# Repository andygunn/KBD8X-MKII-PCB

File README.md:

# KBD8X-MKII-PCB
This is the source for the PCB used in the [KBD8X MKII by KBDfans](https://kbdfans.com/collections/kbd8x-mkii/products/coming-soon-kbd8x-mkii-custom-mechanical-keyboard-kit) by [ai03](https://kb.ai03.me). There have been a number of modifications to this PCB:
- Changed the MX-only footprints to MX/Alps-compatible footprints.
- Modified the routing of traces to accomodate the new footprints.
- Changed the ATmega32U4 from the -MU variety to the -AU variety so it could be hand-soldered (due to component shortages)

This PCB should work with the same firmware files as the original PCB, as the MCU and matrix are the same.

Note that this PCB is offered as-is with NO WARRANTY. If you produce it, you may encounter problems.

Please verify the conditions of the [license](https://github.com/ai03-2725/KBD8X-MKII-PCB/blob/master/LICENSE) before using.

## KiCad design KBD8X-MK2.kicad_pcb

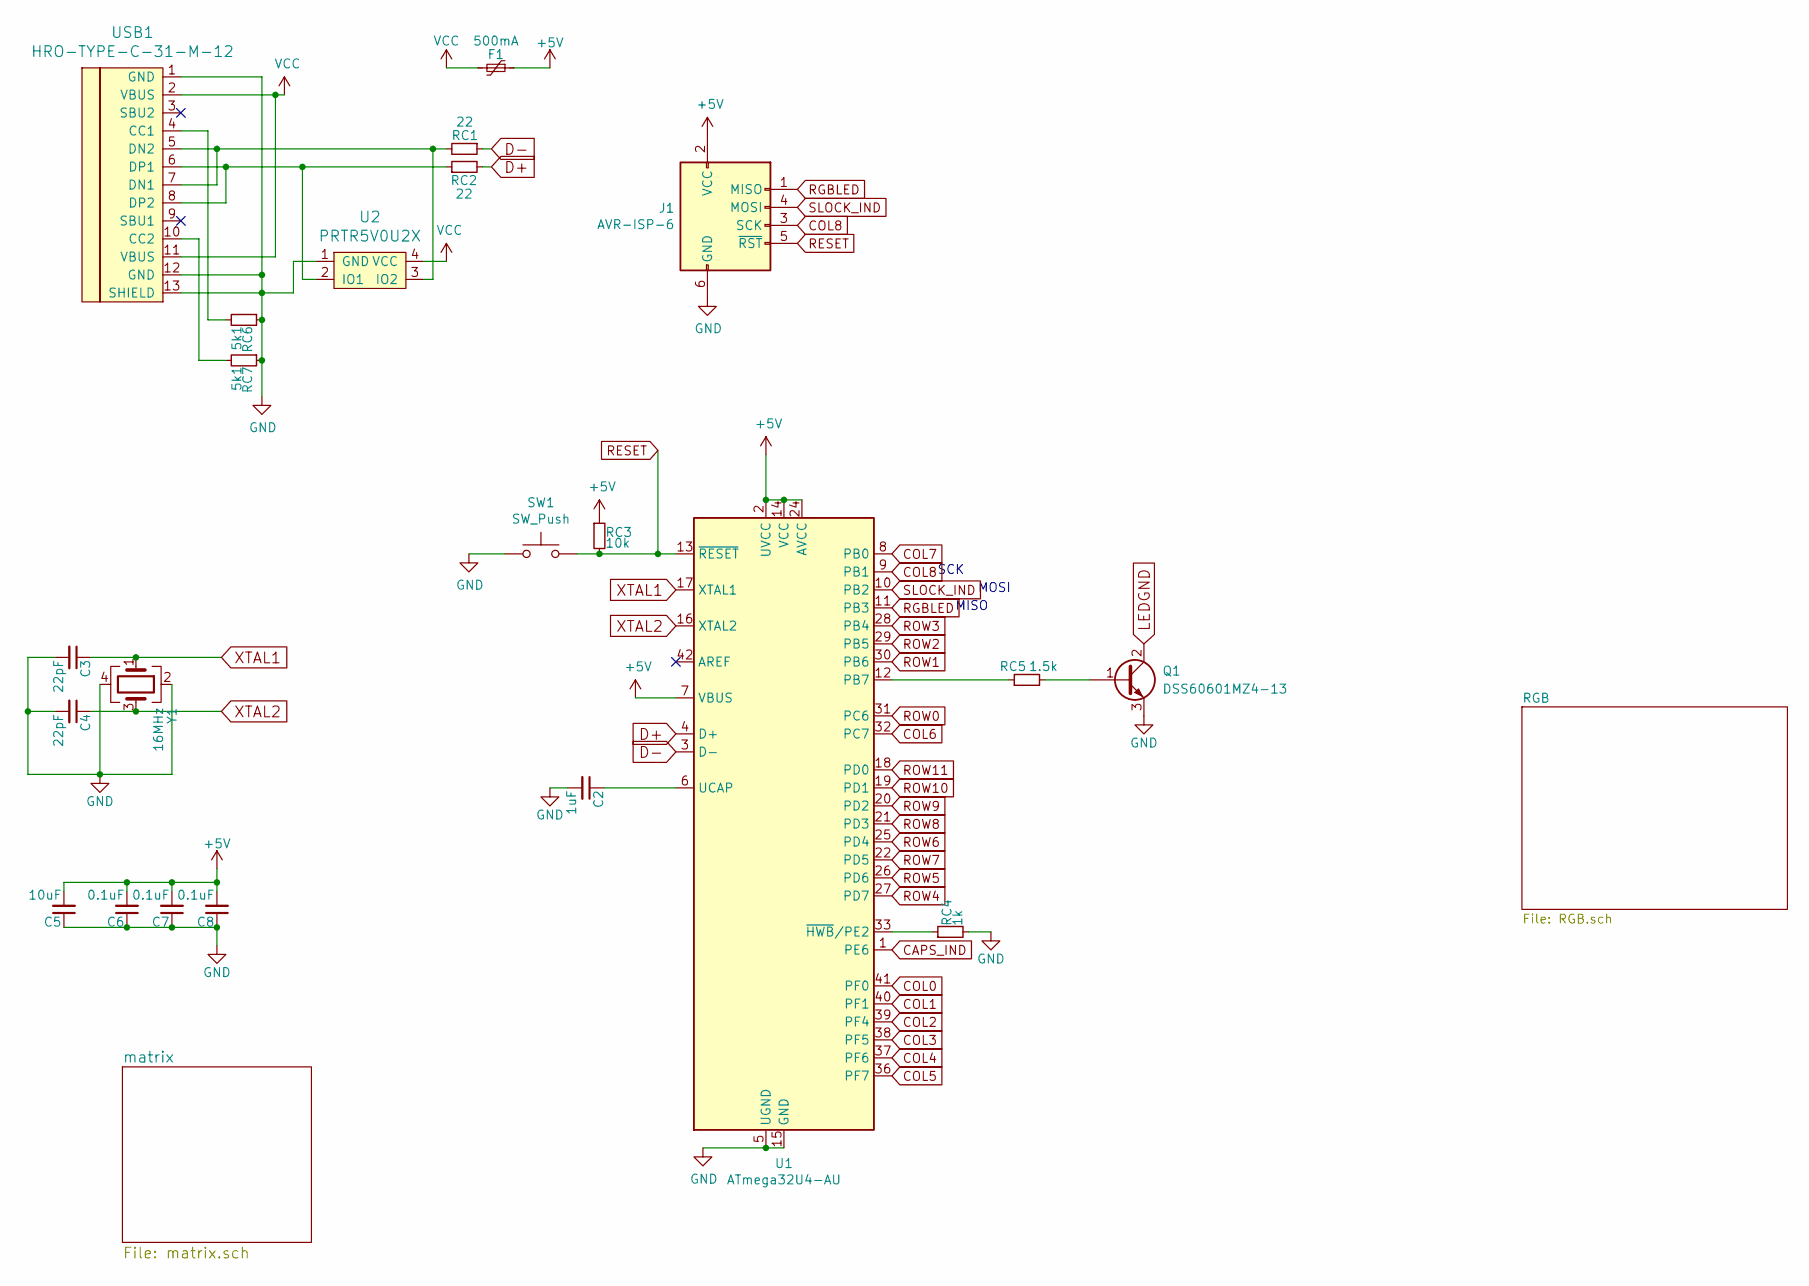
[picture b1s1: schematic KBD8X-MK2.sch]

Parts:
C2: 1uF; C_0603
C3, C4: 22pF; C_0603
C5: 10uF; C_0603
C6, C7, C8: 0.1uF; C_0603
F1: 500mA; Fuse_SMD1206_Wave
J1: AVR-ISP-6; Reset_Pretty-Mask
Q1: DSS60601MZ4-13; SOT-223-3_TabPin2
RC1, RC2: 22; R_0603
RC3: 10k; R_0603
RC4: 1k; R_0603
RC5: 1.5k; R_0603
RC6, RC7: 5k1; R_0603
SW1: SW_Push; SKQG-1155865
U1: ATmega32U4-AU; TQFP-44_10x10mm_P0.8mm
U2: PRTR5V0U2X; SOT143B
USB1: HRO-TYPE-C-31-M-12; HRO-TYPE-C-31-M-12-Assembly
Y1: 16MHz; Crystal_SMD_3225-4pin_3.2x2.5mm

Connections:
+5V: C5.2, C6.2, C7.2, C8.2, F1.1, J1.2 (VCC), RC3.1, U1.2 (UVCC), U1.7 (VBUS), U1.14 (VCC), U1.24 (AVCC), U1.34 (VCC), U1.44 (AVCC); also elsewhere on the board
CAPS_IND: U1.1 (PE6); also elsewhere on the board
COL0: U1.41 (PF0); also elsewhere on the board
COL1: U1.40 (PF1); also elsewhere on the board
COL2: U1.39 (PF4); also elsewhere on the board
COL3: U1.38 (PF5); also elsewhere on the board
COL4: U1.37 (PF6); also elsewhere on the board
COL5: U1.36 (PF7); also elsewhere on the board
COL6: U1.32 (PC7); also elsewhere on the board
COL7: U1.8 (PB0); also elsewhere on the board
COL8: J1.3 (SCK), U1.9 (PB1); also elsewhere on the board
D+: RC2.2, U1.4 (D+)
D-: RC1.1, U1.3 (D-)
GND: C2.2, C3.2, C4.2, C5.1, C6.1, C7.1, C8.1, J1.6 (GND), Q1.3 (E), RC4.2, RC6.1, RC7.1, SW1.1, U1.5 (UGND), U1.15 (GND), U1.23 (GND), U1.35 (GND), U1.43 (GND), U1.45 (GND), U2.1 (GND), USB1.1 (GND), USB1.12 (GND), USB1.13 (SHIELD), Y1.2, Y1.4; also elsewhere on the board
LEDGND: Q1.2 (C); also elsewhere on the board
unnamed: C2.1, U1.6 (UCAP)
unnamed: Q1.1 (B), RC5.2
unnamed: RC1.2, U2.3 (IO2), USB1.5 (DN2), USB1.7 (DN1)
unnamed: RC2.1, U2.2 (IO1), USB1.6 (DP1), USB1.8 (DP2)
unnamed: RC4.1, U1.33 (~HWB~/PE2)
unnamed: RC5.1, U1.12 (PB7)
unnamed: RC6.2, USB1.4 (CC1)
unnamed: RC7.2, USB1.10 (CC2)
RESET: J1.5 (~RST), RC3.2, SW1.2, U1.13 (~RESET)
RGBLED: J1.1 (MISO), U1.11 (PB3); also elsewhere on the board
ROW0: U1.31 (PC6); also elsewhere on the board
ROW1: U1.30 (PB6); also elsewhere on the board
ROW2: U1.29 (PB5); also elsewhere on the board
ROW3: U1.28 (PB4); also elsewhere on the board
ROW4: U1.27 (PD7); also elsewhere on the board
ROW5: U1.26 (PD6); also elsewhere on the board
ROW6: U1.25 (PD4); also elsewhere on the board
ROW7: U1.22 (PD5); also elsewhere on the board
ROW8: U1.21 (PD3); also elsewhere on the board
ROW9: U1.20 (PD2); also elsewhere on the board
ROW10: U1.19 (PD1); also elsewhere on the board
ROW11: U1.18 (PD0); also elsewhere on the board
SLOCK_IND: J1.4 (MOSI), U1.10 (PB2); also elsewhere on the board
VCC: F1.2, U2.4 (VCC), USB1.2 (VBUS), USB1.11 (VBUS)
XTAL1: C3.1, U1.17 (XTAL1), Y1.1
XTAL2: C4.1, U1.16 (XTAL2), Y1.3

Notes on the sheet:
MOSI
MISO
SCK

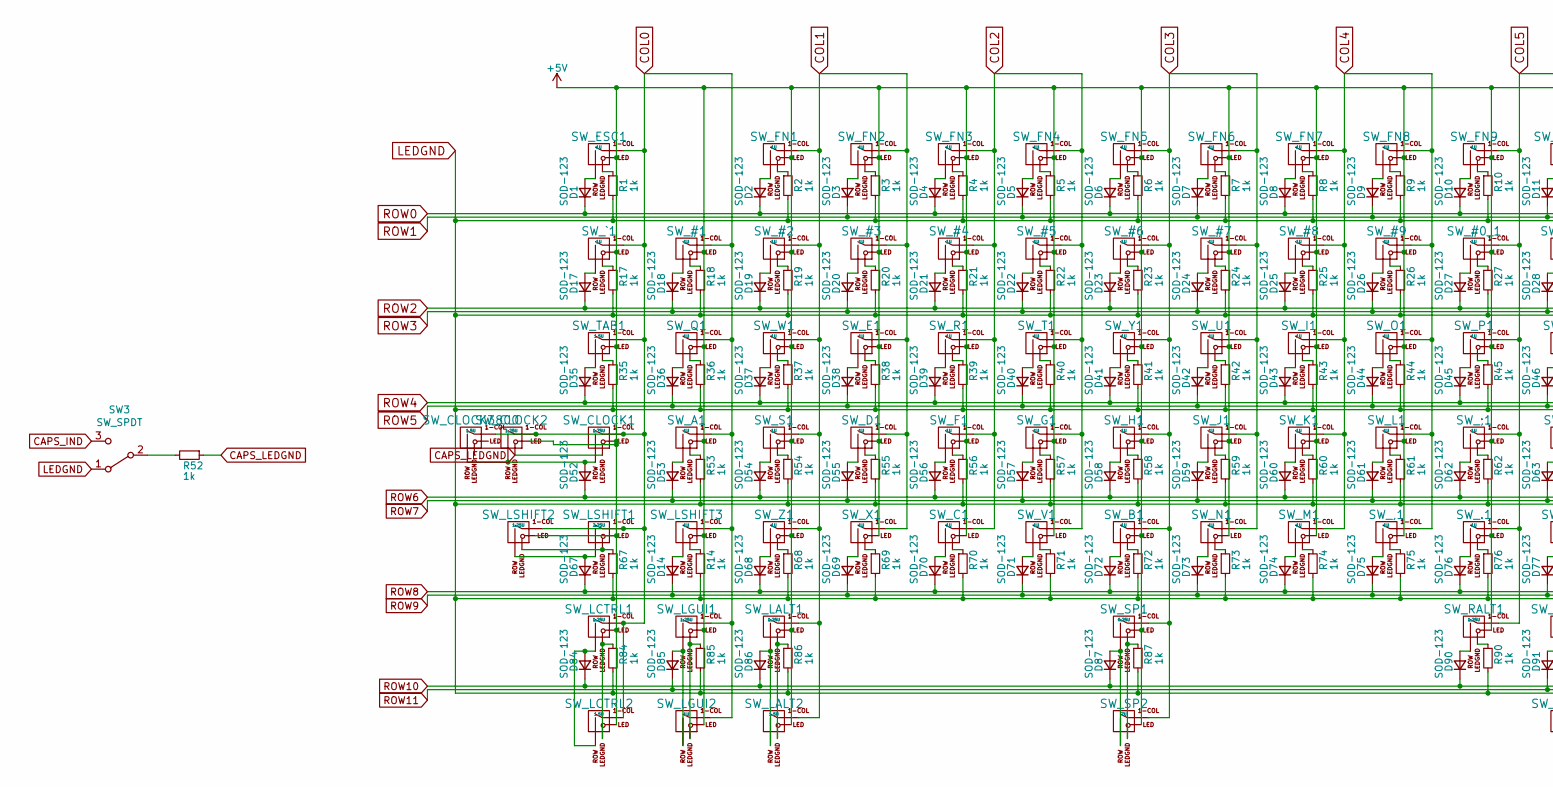
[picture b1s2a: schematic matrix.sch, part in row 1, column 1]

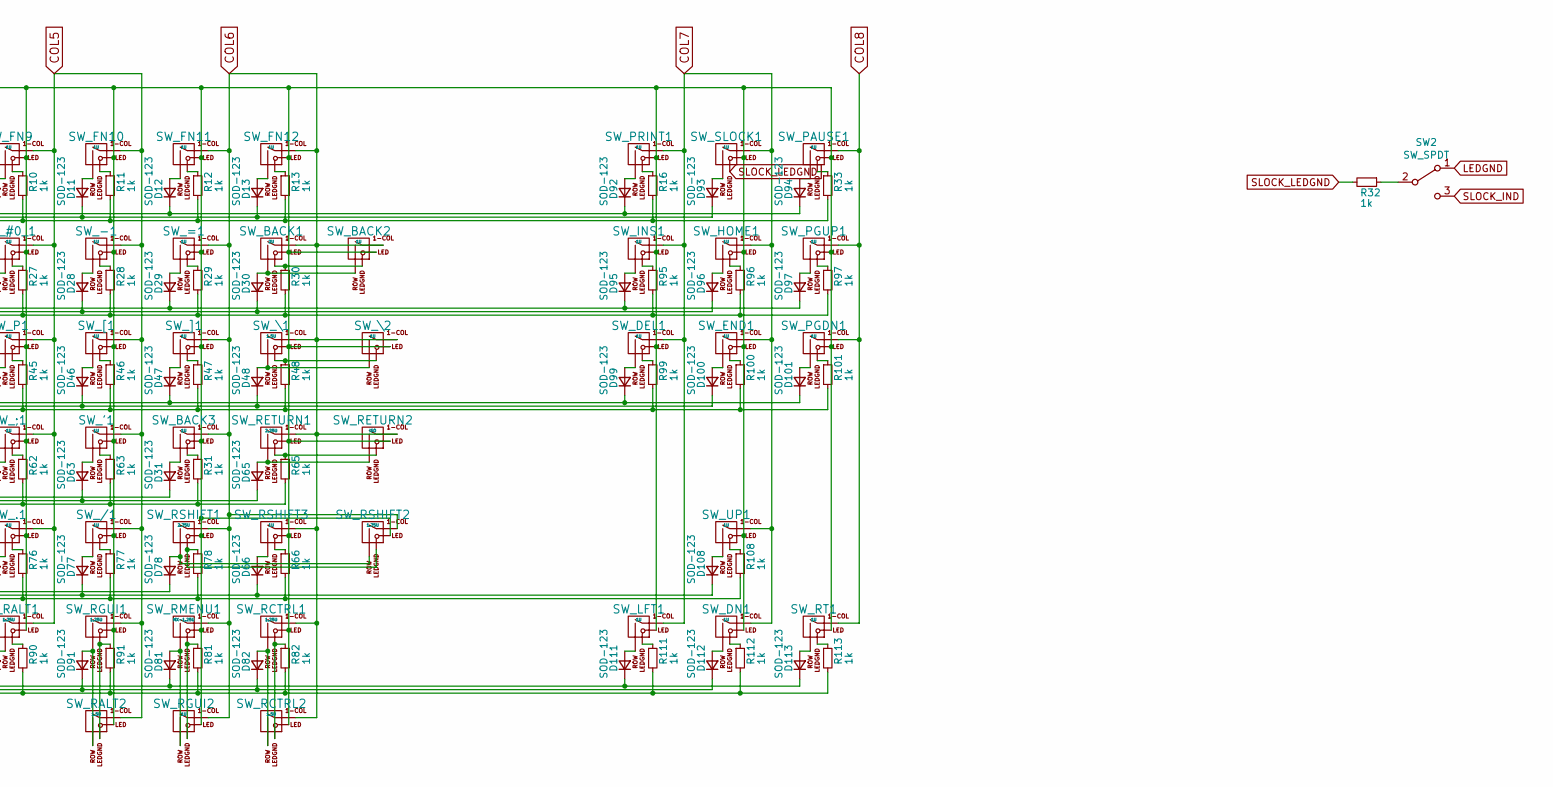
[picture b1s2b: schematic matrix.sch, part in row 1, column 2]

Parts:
D1, D2, D3, D4, D5, D6, D7, D8, D9, D10, D11, D12, D13, D14, D17, D18, D19, D20, D21, D22, D23, D24, D25, D26, D27, D28, D29, D30, D31, D35, D36, D37, D38, D39, D40, D41, D42, D43, D44, D45, D46, D47, D48, D52, D53, D54, D55, D56, D57, D58, D59, D60, D61, D62, D63, D65, D66, D67, D68, D69, D70, D71, D72, D73, D74, D75, D76, D77, D78, D81, D82, D84, D85, D86, D87, D90, D91, D92, D93, D94, D95, D96, D97, D99, D100, D101, D108, D111, D112, D113: SOD-123; D_SOD-123
R1, R2, R3, R4, R5, R6, R7, R8, R9, R10, R11, R12, R13, R14, R16, R17, R18, R19, R20, R21, R22, R23, R24, R25, R26, R27, R28, R29, R30, R31, R32, R33, R35, R36, R37, R38, R39, R40, R41, R42, R43, R44, R45, R46, R47, R48, R52, R53, R54, R55, R56, R57, R58, R59, R60, R61, R62, R63, R65, R66, R67, R68, R69, R70, R71, R72, R73, R74, R75, R76, R77, R78, R81, R82, R84, R85, R86, R87, R90, R91, R95, R96, R97, R99, R100, R101, R108, R111, R112, R113: 1k; R_0603
SW2, SW3: SW_SPDT; SW_SPDT_PCM12
SW_#0_1, SW_#1, SW_#2, SW_#3, SW_#4, SW_#5, SW_#6, SW_#7, SW_#8, SW_#9: 1U; MX-1U
SW_'1: 1U; MX-1U
SW_,1: 1U; MX-1U
SW_-1: 1U; MX-1U
SW_.1: 1U; MX-1U
SW_/1: 1U; MX-1U
SW_;1: 1U; MX-1U
SW_=1: 1U; MX-1U
SW_A1: 1U; MX-1U
SW_B1: 1U; MX-1U
SW_BACK1: 2U; MX-2U
SW_BACK2, SW_BACK3: 1U; MX-1U
SW_C1: 1U; MX-1U
SW_CLOCK1: 1.75U; MX-1.75U
SW_CLOCK2: 1.25U; MX-1.25U-FLIPPED
SW_CLOCK3800: 1.5U; ALPS-1.5U
SW_D1: 1U; MX-1U
SW_DEL1: 1U; MX-1U
SW_DN1: 1U; MX-1U
SW_E1: 1U; MX-1U
SW_END1: 1U; MX-1U
SW_ESC1: 1U; MX-1U
SW_F1: 1U; MX-1U
SW_FN1, SW_FN2, SW_FN3, SW_FN4, SW_FN5, SW_FN6, SW_FN7, SW_FN8, SW_FN9, SW_FN10, SW_FN11, SW_FN12: 1U; MX-1U
SW_G1: 1U; MX-1U
SW_H1: 1U; MX-1U
SW_HOME1: 1U; MX-1U
SW_I1: 1U; MX-1U
SW_INS1: 1U; MX-1U
SW_J1: 1U; MX-1U
SW_K1: 1U; MX-1U
SW_L1: 1U; MX-1U
SW_LALT1: 1.25U; MX-1.25U
SW_LALT2: 1.5U; MX-1.5U-FLIPPED
SW_LCTRL1: 1.25U; MX-1.25U
SW_LCTRL2: 1.5U; MX-1.5U-FLIPPED
SW_LFT1: 1U; MX-1U
SW_LGUI1: 1.25U; MX-1.25U
SW_LGUI2: 1U; MX-1U-FLIPPED
SW_LSHIFT1: 2.25U; MX-2.25U
SW_LSHIFT2: 1.25U; MX-1.25U
SW_LSHIFT3: 1U; MX-1U
SW_M1: 1U; MX-1U
SW_N1: 1U; MX-1U
SW_O1: 1U; MX-1U
SW_P1: 1U; MX-1U
SW_PAUSE1: 1U; MX-1U
SW_PGDN1: 1U; MX-1U
SW_PGUP1: 1U; MX-1U
SW_PRINT1: 1U; MX-1U
SW_Q1: 1U; MX-1U
SW_R1: 1U; MX-1U
SW_RALT1: 1.25U; MX-1.25U
SW_RALT2: 1.5U; MX-1.5U
SW_RCTRL1: 1.25U; MX-1.25U-FLIPPED
SW_RCTRL2: 1.5U; MX-1.5U
SW_RETURN1: 2.25U; MX-2.25U
SW_RETURN2: ISO; MX-ISO-ReversedStabilizers
SW_RGUI1: 1.25U; MX-1.25U-FLIPPED
SW_RGUI2: 1U; MX-1U
SW_RMENU1: MX-1.25U; MX-1.25U-FLIPPED
SW_RSHIFT1: 2.75U; MX-2.75U
SW_RSHIFT2: 1.75U; MX-1.75U
SW_RSHIFT3: 1U; MX-1U
SW_RT1: 1U; MX-1U
SW_S1: 1U; MX-1U
SW_SLOCK1: 1U; MX-1U
SW_SP1: 6.25U; MX-6.25U-ReversedStabilizers
SW_SP2: 7U; MX-7U-ReversedStabilizers
SW_T1: 1U; MX-1U
SW_TAB1: 1.5U; MX-1.5U
SW_U1: 1U; MX-1U
SW_UP1: 1U; MX-1U
SW_V1: 1U; MX-1U
SW_W1: 1U; MX-1U
SW_X1: 1U; MX-1U
SW_Y1: 1U; MX-1U
SW_Z1: 1U; MX-1U
SW_[1: 1U; MX-1U
SW_\1: 1.5U; MX-1.5U
SW_\2: 1U; MX-1U
SW_]1: 1U; MX-1U
SW_`1: 1U; MX-1U

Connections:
+5V: SW_#0_1.3 (LED), SW_#1.3 (LED), SW_#2.3 (LED), SW_#3.3 (LED), SW_#4.3 (LED), SW_#5.3 (LED), SW_#6.3 (LED), SW_#7.3 (LED), SW_#8.3 (LED), SW_#9.3 (LED), SW_'1.3 (LED), SW_,1.3 (LED), SW_-1.3 (LED), SW_.1.3 (LED), SW_/1.3 (LED), SW_;1.3 (LED), SW_=1.3 (LED), SW_A1.3 (LED), SW_B1.3 (LED), SW_BACK1.3 (LED), SW_BACK2.3 (LED), SW_BACK3.3 (LED), SW_C1.3 (LED), SW_CLOCK1.3 (LED), SW_CLOCK2.3 (LED), SW_D1.3 (LED), SW_DEL1.3 (LED), SW_DN1.3 (LED), SW_E1.3 (LED), SW_END1.3 (LED), SW_ESC1.3 (LED), SW_F1.3 (LED), SW_FN1.3 (LED), SW_FN2.3 (LED), SW_FN3.3 (LED), SW_FN4.3 (LED), SW_FN5.3 (LED), SW_FN6.3 (LED), SW_FN7.3 (LED), SW_FN8.3 (LED), SW_FN9.3 (LED), SW_FN10.3 (LED), SW_FN11.3 (LED), SW_FN12.3 (LED), SW_G1.3 (LED), SW_H1.3 (LED), SW_HOME1.3 (LED), SW_I1.3 (LED), SW_INS1.3 (LED), SW_J1.3 (LED), SW_K1.3 (LED), SW_L1.3 (LED), SW_LALT1.3 (LED), SW_LALT2.3 (LED), SW_LCTRL1.3 (LED), SW_LCTRL2.3 (LED), SW_LFT1.3 (LED), SW_LGUI1.3 (LED), SW_LGUI2.3 (LED), SW_LSHIFT1.3 (LED), SW_LSHIFT2.3 (LED), SW_LSHIFT3.3 (LED), SW_M1.3 (LED), SW_N1.3 (LED), SW_O1.3 (LED), SW_P1.3 (LED), SW_PAUSE1.3 (LED), SW_PGDN1.3 (LED), SW_PGUP1.3 (LED), SW_PRINT1.3 (LED), SW_Q1.3 (LED), SW_R1.3 (LED), SW_RALT1.3 (LED), SW_RALT2.3 (LED), SW_RCTRL1.3 (LED), SW_RCTRL2.3 (LED), SW_RETURN1.3 (LED), SW_RETURN2.3 (LED), SW_RGUI1.3 (LED), SW_RGUI2.3 (LED), SW_RMENU1.3 (LED), SW_RSHIFT1.3 (LED), SW_RSHIFT2.3 (LED), SW_RSHIFT3.3 (LED), SW_RT1.3 (LED), SW_S1.3 (LED), SW_SLOCK1.3 (LED), SW_SP1.3 (LED), SW_SP2.3 (LED), SW_T1.3 (LED), SW_TAB1.3 (LED), SW_U1.3 (LED), SW_UP1.3 (LED), SW_V1.3 (LED), SW_W1.3 (LED), SW_X1.3 (LED), SW_Y1.3 (LED), SW_Z1.3 (LED), SW_[1.3 (LED), SW_\1.3 (LED), SW_\2.3 (LED), SW_]1.3 (LED), SW_`1.3 (LED); also elsewhere on the board
CAPS_IND: SW3.3 (C); also elsewhere on the board
CAPS_LEDGND: R52.1, SW_CLOCK1.4 (LEDGND), SW_CLOCK2.4 (LEDGND)
COL0: SW_#1.1 (COL), SW_A1.1 (COL), SW_CLOCK1.1 (COL), SW_CLOCK2.1 (COL), SW_CLOCK3800.1 (COL), SW_ESC1.1 (COL), SW_LCTRL1.1 (COL), SW_LCTRL2.1 (COL), SW_LGUI1.1 (COL), SW_LGUI2.1 (COL), SW_LSHIFT1.1 (COL), SW_LSHIFT2.1 (COL), SW_LSHIFT3.1 (COL), SW_Q1.1 (COL), SW_TAB1.1 (COL), SW_`1.1 (COL); also elsewhere on the board
COL1: SW_#2.1 (COL), SW_#3.1 (COL), SW_D1.1 (COL), SW_E1.1 (COL), SW_FN1.1 (COL), SW_FN2.1 (COL), SW_LALT1.1 (COL), SW_LALT2.1 (COL), SW_S1.1 (COL), SW_W1.1 (COL), SW_X1.1 (COL), SW_Z1.1 (COL); also elsewhere on the board
COL2: SW_#4.1 (COL), SW_#5.1 (COL), SW_C1.1 (COL), SW_F1.1 (COL), SW_FN3.1 (COL), SW_FN4.1 (COL), SW_G1.1 (COL), SW_R1.1 (COL), SW_T1.1 (COL), SW_V1.1 (COL); also elsewhere on the board
COL3: SW_#6.1 (COL), SW_#7.1 (COL), SW_B1.1 (COL), SW_FN5.1 (COL), SW_FN6.1 (COL), SW_H1.1 (COL), SW_J1.1 (COL), SW_N1.1 (COL), SW_SP1.1 (COL), SW_SP2.1 (COL), SW_U1.1 (COL), SW_Y1.1 (COL); also elsewhere on the board
COL4: SW_#8.1 (COL), SW_#9.1 (COL), SW_,1.1 (COL), SW_FN7.1 (COL), SW_FN8.1 (COL), SW_I1.1 (COL), SW_K1.1 (COL), SW_L1.1 (COL), SW_M1.1 (COL), SW_O1.1 (COL); also elsewhere on the board
COL5: SW_#0_1.1 (COL), SW_'1.1 (COL), SW_-1.1 (COL), SW_.1.1 (COL), SW_/1.1 (COL), SW_;1.1 (COL), SW_FN9.1 (COL), SW_FN10.1 (COL), SW_P1.1 (COL), SW_RALT1.1 (COL), SW_RALT2.1 (COL), SW_RGUI1.1 (COL), SW_[1.1 (COL); also elsewhere on the board
COL6: SW_=1.1 (COL), SW_BACK1.1 (COL), SW_BACK2.1 (COL), SW_BACK3.1 (COL), SW_FN11.1 (COL), SW_FN12.1 (COL), SW_RCTRL1.1 (COL), SW_RCTRL2.1 (COL), SW_RETURN1.1 (COL), SW_RETURN2.1 (COL), SW_RGUI2.1 (COL), SW_RMENU1.1 (COL), SW_RSHIFT1.1 (COL), SW_RSHIFT2.1 (COL), SW_RSHIFT3.1 (COL), SW_\1.1 (COL), SW_\2.1 (COL), SW_]1.1 (COL); also elsewhere on the board
COL7: SW_DEL1.1 (COL), SW_DN1.1 (COL), SW_END1.1 (COL), SW_HOME1.1 (COL), SW_INS1.1 (COL), SW_LFT1.1 (COL), SW_PRINT1.1 (COL), SW_SLOCK1.1 (COL), SW_UP1.1 (COL); also elsewhere on the board
COL8: SW_PAUSE1.1 (COL), SW_PGDN1.1 (COL), SW_PGUP1.1 (COL), SW_RT1.1 (COL); also elsewhere on the board
LEDGND: R1.2, R2.2, R3.2, R4.2, R5.2, R6.2, R7.2, R8.2, R9.2, R10.2, R11.2, R12.2, R13.2, R14.2, R16.2, R17.2, R18.2, R19.2, R20.2, R21.2, R22.2, R23.2, R24.2, R25.2, R26.2, R27.2, R28.2, R29.2, R30.2, R31.2, R33.2, R35.2, R36.2, R37.2, R38.2, R39.2, R40.2, R41.2, R42.2, R43.2, R44.2, R45.2, R46.2, R47.2, R48.2, R53.2, R54.2, R55.2, R56.2, R57.2, R58.2, R59.2, R60.2, R61.2, R62.2, R63.2, R65.2, R66.2, R67.2, R68.2, R69.2, R70.2, R71.2, R72.2, R73.2, R74.2, R75.2, R76.2, R77.2, R78.2, R81.2, R82.2, R84.2, R85.2, R86.2, R87.2, R90.2, R91.2, R95.2, R96.2, R97.2, R99.2, R100.2, R101.2, R108.2, R111.2, R112.2, R113.2, SW2.1 (A), SW3.1 (A); also elsewhere on the board
unnamed: D1.2 (A), SW_ESC1.2 (ROW)
unnamed: D2.2 (A), SW_FN1.2 (ROW)
unnamed: D3.2 (A), SW_FN2.2 (ROW)
unnamed: D4.2 (A), SW_FN3.2 (ROW)
unnamed: D5.2 (A), SW_FN4.2 (ROW)
unnamed: D6.2 (A), SW_FN5.2 (ROW)
unnamed: D7.2 (A), SW_FN6.2 (ROW)
unnamed: D8.2 (A), SW_FN7.2 (ROW)
unnamed: D9.2 (A), SW_FN8.2 (ROW)
unnamed: D10.2 (A), SW_FN9.2 (ROW)
unnamed: D11.2 (A), SW_FN10.2 (ROW)
unnamed: D12.2 (A), SW_FN11.2 (ROW)
unnamed: D13.2 (A), SW_FN12.2 (ROW)
unnamed: D14.2 (A), SW_LSHIFT3.2 (ROW)
unnamed: D17.2 (A), SW_`1.2 (ROW)
unnamed: D18.2 (A), SW_#1.2 (ROW)
unnamed: D19.2 (A), SW_#2.2 (ROW)
unnamed: D20.2 (A), SW_#3.2 (ROW)
unnamed: D21.2 (A), SW_#4.2 (ROW)
unnamed: D22.2 (A), SW_#5.2 (ROW)
unnamed: D23.2 (A), SW_#6.2 (ROW)
unnamed: D24.2 (A), SW_#7.2 (ROW)
unnamed: D25.2 (A), SW_#8.2 (ROW)
unnamed: D26.2 (A), SW_#9.2 (ROW)
unnamed: D27.2 (A), SW_#0_1.2 (ROW)
unnamed: D28.2 (A), SW_-1.2 (ROW)
unnamed: D29.2 (A), SW_=1.2 (ROW)
unnamed: D30.2 (A), SW_BACK1.2 (ROW), SW_BACK2.2 (ROW)
unnamed: D31.2 (A), SW_BACK3.2 (ROW)
unnamed: D35.2 (A), SW_TAB1.2 (ROW)
unnamed: D36.2 (A), SW_Q1.2 (ROW)
unnamed: D37.2 (A), SW_W1.2 (ROW)
unnamed: D38.2 (A), SW_E1.2 (ROW)
unnamed: D39.2 (A), SW_R1.2 (ROW)
unnamed: D40.2 (A), SW_T1.2 (ROW)
unnamed: D41.2 (A), SW_Y1.2 (ROW)
unnamed: D42.2 (A), SW_U1.2 (ROW)
unnamed: D43.2 (A), SW_I1.2 (ROW)
unnamed: D44.2 (A), SW_O1.2 (ROW)
unnamed: D45.2 (A), SW_P1.2 (ROW)
unnamed: D46.2 (A), SW_[1.2 (ROW)
unnamed: D47.2 (A), SW_]1.2 (ROW)
unnamed: D48.2 (A), SW_\1.2 (ROW), SW_\2.2 (ROW)
unnamed: D52.2 (A), SW_CLOCK1.2 (ROW), SW_CLOCK2.2 (ROW), SW_CLOCK3800.2 (ROW)
unnamed: D53.2 (A), SW_A1.2 (ROW)
unnamed: D54.2 (A), SW_S1.2 (ROW)
unnamed: D55.2 (A), SW_D1.2 (ROW)
unnamed: D56.2 (A), SW_F1.2 (ROW)
unnamed: D57.2 (A), SW_G1.2 (ROW)
unnamed: D58.2 (A), SW_H1.2 (ROW)
unnamed: D59.2 (A), SW_J1.2 (ROW)
unnamed: D60.2 (A), SW_K1.2 (ROW)
unnamed: D61.2 (A), SW_L1.2 (ROW)
unnamed: D62.2 (A), SW_;1.2 (ROW)
unnamed: D63.2 (A), SW_'1.2 (ROW)
unnamed: D65.2 (A), SW_RETURN1.2 (ROW), SW_RETURN2.2 (ROW)
unnamed: D66.2 (A), SW_RSHIFT3.2 (ROW)
unnamed: D67.2 (A), SW_LSHIFT1.2 (ROW), SW_LSHIFT2.2 (ROW)
unnamed: D68.2 (A), SW_Z1.2 (ROW)
unnamed: D69.2 (A), SW_X1.2 (ROW)
unnamed: D70.2 (A), SW_C1.2 (ROW)
unnamed: D71.2 (A), SW_V1.2 (ROW)
unnamed: D72.2 (A), SW_B1.2 (ROW)
unnamed: D73.2 (A), SW_N1.2 (ROW)
unnamed: D74.2 (A), SW_M1.2 (ROW)
unnamed: D75.2 (A), SW_,1.2 (ROW)
unnamed: D76.2 (A), SW_.1.2 (ROW)
unnamed: D77.2 (A), SW_/1.2 (ROW)
unnamed: D78.2 (A), SW_RSHIFT1.2 (ROW), SW_RSHIFT2.2 (ROW)
unnamed: D81.2 (A), SW_RGUI2.2 (ROW), SW_RMENU1.2 (ROW)
unnamed: D82.2 (A), SW_RCTRL1.2 (ROW), SW_RCTRL2.2 (ROW)
unnamed: D84.2 (A), SW_LCTRL1.2 (ROW), SW_LCTRL2.2 (ROW)
unnamed: D85.2 (A), SW_LGUI1.2 (ROW), SW_LGUI2.2 (ROW)
unnamed: D86.2 (A), SW_LALT1.2 (ROW), SW_LALT2.2 (ROW)
unnamed: D87.2 (A), SW_SP1.2 (ROW), SW_SP2.2 (ROW)
unnamed: D90.2 (A), SW_RALT1.2 (ROW)
unnamed: D91.2 (A), SW_RALT2.2 (ROW), SW_RGUI1.2 (ROW)
unnamed: D92.2 (A), SW_PRINT1.2 (ROW)
unnamed: D93.2 (A), SW_SLOCK1.2 (ROW)
unnamed: D94.2 (A), SW_PAUSE1.2 (ROW)
unnamed: D95.2 (A), SW_INS1.2 (ROW)
unnamed: D96.2 (A), SW_HOME1.2 (ROW)
unnamed: D97.2 (A), SW_PGUP1.2 (ROW)
unnamed: D99.2 (A), SW_DEL1.2 (ROW)
unnamed: D100.2 (A), SW_END1.2 (ROW)
unnamed: D101.2 (A), SW_PGDN1.2 (ROW)
unnamed: D108.2 (A), SW_UP1.2 (ROW)
unnamed: D111.2 (A), SW_LFT1.2 (ROW)
unnamed: D112.2 (A), SW_DN1.2 (ROW)
unnamed: D113.2 (A), SW_RT1.2 (ROW)
unnamed: R1.1, SW_ESC1.4 (LEDGND)
unnamed: R2.1, SW_FN1.4 (LEDGND)
unnamed: R3.1, SW_FN2.4 (LEDGND)
unnamed: R4.1, SW_FN3.4 (LEDGND)
unnamed: R5.1, SW_FN4.4 (LEDGND)
unnamed: R6.1, SW_FN5.4 (LEDGND)
unnamed: R7.1, SW_FN6.4 (LEDGND)
unnamed: R8.1, SW_FN7.4 (LEDGND)
unnamed: R9.1, SW_FN8.4 (LEDGND)
unnamed: R10.1, SW_FN9.4 (LEDGND)
unnamed: R11.1, SW_FN10.4 (LEDGND)
unnamed: R12.1, SW_FN11.4 (LEDGND)
unnamed: R13.1, SW_FN12.4 (LEDGND)
unnamed: R14.1, SW_LSHIFT3.4 (LEDGND)
unnamed: R16.1, SW_PRINT1.4 (LEDGND)
unnamed: R17.1, SW_`1.4 (LEDGND)
unnamed: R18.1, SW_#1.4 (LEDGND)
unnamed: R19.1, SW_#2.4 (LEDGND)
unnamed: R20.1, SW_#3.4 (LEDGND)
unnamed: R21.1, SW_#4.4 (LEDGND)
unnamed: R22.1, SW_#5.4 (LEDGND)
unnamed: R23.1, SW_#6.4 (LEDGND)
unnamed: R24.1, SW_#7.4 (LEDGND)
unnamed: R25.1, SW_#8.4 (LEDGND)
unnamed: R26.1, SW_#9.4 (LEDGND)
unnamed: R27.1, SW_#0_1.4 (LEDGND)
unnamed: R28.1, SW_-1.4 (LEDGND)
unnamed: R29.1, SW_=1.4 (LEDGND)
unnamed: R30.1, SW_BACK1.4 (LEDGND), SW_BACK2.4 (LEDGND)
unnamed: R31.1, SW_BACK3.4 (LEDGND)
unnamed: R32.1, SW2.2 (B)
unnamed: R33.1, SW_PAUSE1.4 (LEDGND)
unnamed: R35.1, SW_TAB1.4 (LEDGND)
unnamed: R36.1, SW_Q1.4 (LEDGND)
unnamed: R37.1, SW_W1.4 (LEDGND)
unnamed: R38.1, SW_E1.4 (LEDGND)
unnamed: R39.1, SW_R1.4 (LEDGND)
unnamed: R40.1, SW_T1.4 (LEDGND)
unnamed: R41.1, SW_Y1.4 (LEDGND)
unnamed: R42.1, SW_U1.4 (LEDGND)
unnamed: R43.1, SW_I1.4 (LEDGND)
unnamed: R44.1, SW_O1.4 (LEDGND)
unnamed: R45.1, SW_P1.4 (LEDGND)
unnamed: R46.1, SW_[1.4 (LEDGND)
unnamed: R47.1, SW_]1.4 (LEDGND)
unnamed: R48.1, SW_\1.4 (LEDGND), SW_\2.4 (LEDGND)
unnamed: R52.2, SW3.2 (B)
unnamed: R53.1, SW_A1.4 (LEDGND)
unnamed: R54.1, SW_S1.4 (LEDGND)
unnamed: R55.1, SW_D1.4 (LEDGND)
unnamed: R56.1, SW_F1.4 (LEDGND)
unnamed: R57.1, SW_G1.4 (LEDGND)
unnamed: R58.1, SW_H1.4 (LEDGND)
unnamed: R59.1, SW_J1.4 (LEDGND)
unnamed: R60.1, SW_K1.4 (LEDGND)
unnamed: R61.1, SW_L1.4 (LEDGND)
unnamed: R62.1, SW_;1.4 (LEDGND)
unnamed: R63.1, SW_'1.4 (LEDGND)
unnamed: R65.1, SW_RETURN1.4 (LEDGND), SW_RETURN2.4 (LEDGND)
unnamed: R66.1, SW_RSHIFT3.4 (LEDGND)
unnamed: R67.1, SW_LSHIFT1.4 (LEDGND), SW_LSHIFT2.4 (LEDGND)
unnamed: R68.1, SW_Z1.4 (LEDGND)
unnamed: R69.1, SW_X1.4 (LEDGND)
unnamed: R70.1, SW_C1.4 (LEDGND)
unnamed: R71.1, SW_V1.4 (LEDGND)
unnamed: R72.1, SW_B1.4 (LEDGND)
unnamed: R73.1, SW_N1.4 (LEDGND)
unnamed: R74.1, SW_M1.4 (LEDGND)
unnamed: R75.1, SW_,1.4 (LEDGND)
unnamed: R76.1, SW_.1.4 (LEDGND)
unnamed: R77.1, SW_/1.4 (LEDGND)
unnamed: R78.1, SW_RSHIFT1.4 (LEDGND), SW_RSHIFT2.4 (LEDGND)
unnamed: R81.1, SW_RGUI2.4 (LEDGND), SW_RMENU1.4 (LEDGND)
unnamed: R82.1, SW_RCTRL1.4 (LEDGND), SW_RCTRL2.4 (LEDGND)
unnamed: R84.1, SW_LCTRL1.4 (LEDGND), SW_LCTRL2.4 (LEDGND)
unnamed: R85.1, SW_LGUI1.4 (LEDGND), SW_LGUI2.4 (LEDGND)
unnamed: R86.1, SW_LALT1.4 (LEDGND), SW_LALT2.4 (LEDGND)
unnamed: R87.1, SW_SP1.4 (LEDGND), SW_SP2.4 (LEDGND)
unnamed: R90.1, SW_RALT1.4 (LEDGND)
unnamed: R91.1, SW_RALT2.4 (LEDGND), SW_RGUI1.4 (LEDGND)
unnamed: R95.1, SW_INS1.4 (LEDGND)
unnamed: R96.1, SW_HOME1.4 (LEDGND)
unnamed: R97.1, SW_PGUP1.4 (LEDGND)
unnamed: R99.1, SW_DEL1.4 (LEDGND)
unnamed: R100.1, SW_END1.4 (LEDGND)
unnamed: R101.1, SW_PGDN1.4 (LEDGND)
unnamed: R108.1, SW_UP1.4 (LEDGND)
unnamed: R111.1, SW_LFT1.4 (LEDGND)
unnamed: R112.1, SW_DN1.4 (LEDGND)
unnamed: R113.1, SW_RT1.4 (LEDGND)
ROW0: D1.1 (K), D2.1 (K), D4.1 (K), D6.1 (K), D8.1 (K), D10.1 (K), D12.1 (K), D92.1 (K), D94.1 (K); also elsewhere on the board
ROW1: D3.1 (K), D5.1 (K), D7.1 (K), D9.1 (K), D11.1 (K), D13.1 (K), D93.1 (K); also elsewhere on the board
ROW2: D17.1 (K), D19.1 (K), D21.1 (K), D23.1 (K), D25.1 (K), D27.1 (K), D29.1 (K), D95.1 (K), D97.1 (K); also elsewhere on the board
ROW3: D18.1 (K), D20.1 (K), D22.1 (K), D24.1 (K), D26.1 (K), D28.1 (K), D30.1 (K), D96.1 (K); also elsewhere on the board
ROW4: D35.1 (K), D37.1 (K), D39.1 (K), D41.1 (K), D43.1 (K), D45.1 (K), D47.1 (K), D99.1 (K), D101.1 (K); also elsewhere on the board
ROW5: D36.1 (K), D38.1 (K), D40.1 (K), D42.1 (K), D44.1 (K), D46.1 (K), D48.1 (K), D100.1 (K); also elsewhere on the board
ROW6: D31.1 (K), D52.1 (K), D54.1 (K), D56.1 (K), D58.1 (K), D60.1 (K), D62.1 (K); also elsewhere on the board
ROW7: D53.1 (K), D55.1 (K), D57.1 (K), D59.1 (K), D61.1 (K), D63.1 (K), D65.1 (K); also elsewhere on the board
ROW8: D67.1 (K), D68.1 (K), D70.1 (K), D72.1 (K), D74.1 (K), D76.1 (K), D78.1 (K); also elsewhere on the board
ROW9: D14.1 (K), D66.1 (K), D69.1 (K), D71.1 (K), D73.1 (K), D75.1 (K), D77.1 (K), D108.1 (K); also elsewhere on the board
ROW10: D81.1 (K), D84.1 (K), D86.1 (K), D87.1 (K), D90.1 (K), D111.1 (K), D113.1 (K); also elsewhere on the board
ROW11: D82.1 (K), D85.1 (K), D91.1 (K), D112.1 (K); also elsewhere on the board
SLOCK_IND: SW2.3 (C); also elsewhere on the board
SLOCK_LEDGND: R32.2, SW_SLOCK1.4 (LEDGND)

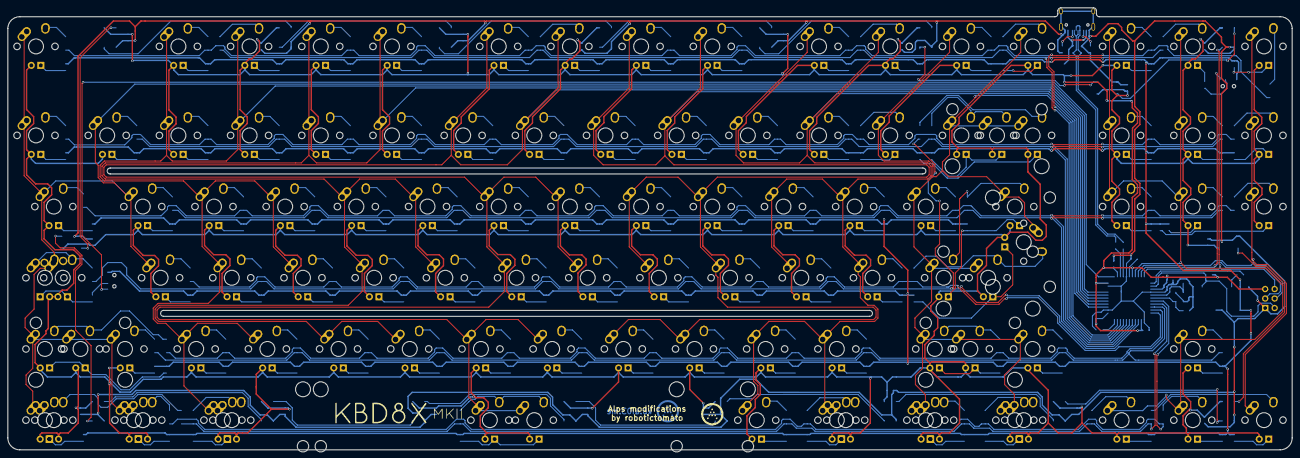
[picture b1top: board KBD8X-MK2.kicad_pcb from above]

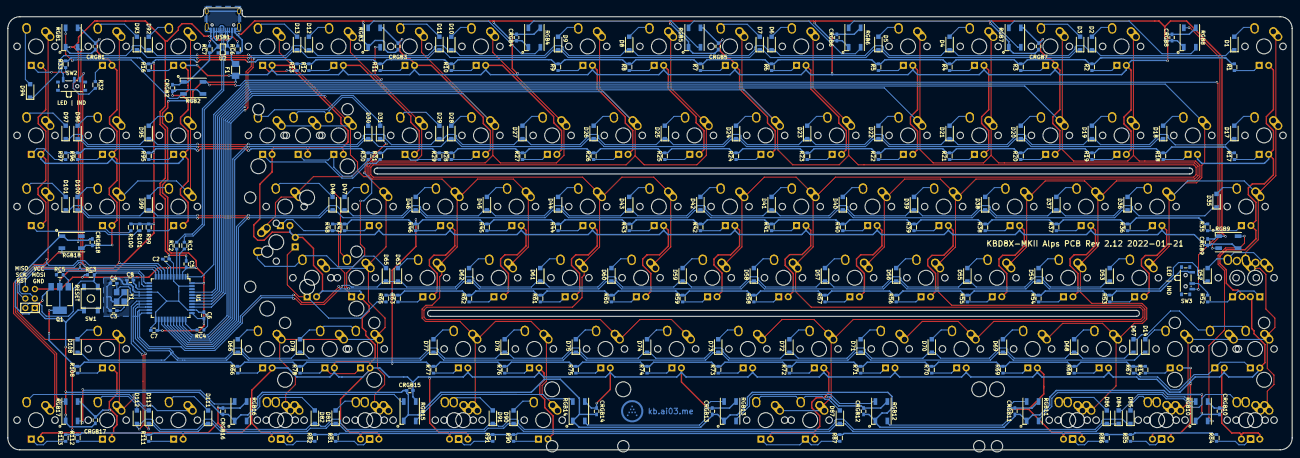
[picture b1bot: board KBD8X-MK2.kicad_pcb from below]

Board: 2 copper layers, 343.7 x 118.3 mm, 344 parts (240 on the bottom side), 240 nets.

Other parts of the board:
CRGB1, CRGB2, CRGB3, CRGB4, CRGB5, CRGB6, CRGB7, CRGB8, CRGB9, CRGB10, CRGB11, CRGB12, CRGB13, CRGB14, CRGB15, CRGB16, CRGB17, CRGB18: 0.1uF; C_0603
RGB1, RGB2, RGB3, RGB4, RGB5, RGB6, RGB7, RGB8, RGB9, RGB10, RGB11, RGB12, RGB13, RGB14, RGB15, RGB16, RGB17, RGB18: WS2812B; LED_WS2812B-PLCC4

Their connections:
+5V: CRGB1.1, CRGB2.1, CRGB3.1, CRGB4.1, CRGB5.1, CRGB6.1, CRGB7.1, CRGB8.1, CRGB9.1, CRGB10.1, CRGB11.1, CRGB12.1, CRGB13.1, CRGB14.1, CRGB15.1, CRGB16.1, CRGB17.1, CRGB18.1, RGB1.1, RGB2.1, RGB3.1, RGB4.1, RGB5.1, RGB6.1, RGB7.1, RGB8.1, RGB9.1, RGB10.1, RGB11.1, RGB12.1, RGB13.1, RGB14.1, RGB15.1, RGB16.1, RGB17.1, RGB18.1; also elsewhere on the board
GND: CRGB1.2, CRGB2.2, CRGB3.2, CRGB4.2, CRGB5.2, CRGB6.2, CRGB7.2, CRGB8.2, CRGB9.2, CRGB10.2, CRGB11.2, CRGB12.2, CRGB13.2, CRGB14.2, CRGB15.2, CRGB16.2, CRGB17.2, CRGB18.2, RGB1.3, RGB2.3, RGB3.3, RGB4.3, RGB5.3, RGB6.3, RGB7.3, RGB8.3, RGB9.3, RGB10.3, RGB11.3, RGB12.3, RGB13.3, RGB14.3, RGB15.3, RGB16.3, RGB17.3, RGB18.3; also elsewhere on the board
unnamed: RGB1.2, RGB2.4
unnamed: RGB2.2, RGB3.4
unnamed: RGB3.2, RGB4.4
unnamed: RGB4.2, RGB5.4
unnamed: RGB5.2, RGB6.4
unnamed: RGB6.2, RGB7.4
unnamed: RGB7.2, RGB8.4
unnamed: RGB8.2, RGB9.4
unnamed: RGB10.2, RGB11.4
unnamed: RGB9.2, RGB10.4
unnamed: RGB11.2, RGB12.4
unnamed: RGB12.2, RGB13.4
unnamed: RGB13.2, RGB14.4
unnamed: RGB14.2, RGB15.4
unnamed: RGB15.2, RGB16.4
unnamed: RGB16.2, RGB17.4
unnamed: RGB17.2, RGB18.4
RGBLED: RGB1.4; also elsewhere on the board

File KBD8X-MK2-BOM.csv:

Comment,Designator,Footprint,LCSC
1uF,C2,locallib:C_0603,C15849
22pF,"C3,C4",locallib:C_0603,C1653
10uF,C5,locallib:C_0603,C19702
0.1uF,"CRGB1,CRGB2,CRGB3,CRGB4,CRGB5,C6,CRGB6,C7,CRGB7,C8,CRGB8,CRGB9,CRGB10,CRGB11,CRGB12,CRGB13,CRGB14,CRGB15,CRGB16,CRGB17,CRGB18",locallib:C_0603,C2167300
SOD-323,"D1,D2,D3,D4,D5,D6,D7,D8,D9,D10,D11,D12,D13,D14,D17,D18,D19,D20,D21,D22,D23,D24,D25,D26,D27,D28,D29,D30,D31,D35,D36,D37,D38,D39,D40,D41,D42,D43,D44,D45,D46,D47,D48,D52,D53,D54,D55,D56,D57,D58,D59,D60,D61,D62,D63,D65,D66,D67,D68,D69,D70,D71,D72,D73,D74,D75,D76,D77,D78,D81,D82,D84,D85,D86,D87,D90,D91,D92,D93,D94,D95,D96,D97,D99,D100,D101,D108,D111,D112,D113",locallib:D_SOD-123,C81598
500mA,F1,Fuse_Holders_and_Fuses:Fuse_SMD1206_Wave,C151162
DSS60601MZ4-13,Q1,TO_SOT_Packages_SMD:SOT-223-3_TabPin2,C150451
22,"RC1,RC2",locallib:R_0603,C23345
10k,RC3,locallib:R_0603,C25804
1k,"R1,R2,R3,RC4,R4,R5,R6,R7,R8,R9,R10,R11,R12,R13,R14,R16,R17,R18,R19,R20,R21,R22,R23,R24,R25,R26,R27,R28,R29,R30,R31,R32,R33,R35,R36,R37,R38,R39,R40,R41,R42,R43,R44,R45,R46,R47,R48,R52,R53,R54,R55,R56,R57,R58,R59,R60,R61,R62,R63,R65,R66,R67,R68,R69,R70,R71,R72,R73,R74,R75,R76,R77,R78,R81,R82,R84,R85,R86,R87,R90,R91,R95,R96,R97,R99,R100,R101,R108,R111,R112,R113",locallib:R_0603,C21190
1.5k,RC5,locallib:R_0603,C22843
5k1,"RC6,RC7",locallib:R_0603,C23186
WS2812B,"RGB1,RGB2,RGB3,RGB4,RGB5,RGB6,RGB7,RGB8,RGB9,RGB10,RGB11,RGB12,RGB13,RGB14,RGB15,RGB16,RGB17,RGB18",locallib:LED_WS2812B-PLCC4,C2761795
SW_Push,SW1,random-keyboard-parts:SKQG-1155865,C116647
SW_SPDT,"SW2,SW3",Buttons_Switches_SMD:SW_SPDT_PCM12,C221841
ATmega32U4-MU,U1,locallib:QFN-44-1EP_7x7mm_Pitch0.5mm,C112161
PRTR5V0U2X,U2,locallib:SOT143B,C12333
HRO-TYPE-C-31-M-12,USB1,Type-C:HRO-TYPE-C-31-M-12-Assembly,C165948
16MHz,Y1,locallib:Crystal_SMD_3225-4pin_3.2x2.5mm,C255906

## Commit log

2021-11-23 Footprint updates top two rows
    Footprints have been updated on the top two rows of the PCB to add Alps switch compatibility.
2021-11-24 Additional row footprint update
    Update of a row of footprints from MX only to Alps compatible.
2021-11-24 Additional row of footprint updates
    Enter row footprints updated to Alps compatible.
2021-11-25 Additional footprint updates
2021-11-25 Final footprint updates
    All rows have been updated to Alps compatible switch footprints.
2021-11-25 Gerber file changes
    Removal of the old Gerber file and creation of a new one. A new JPG file was also generated with the changes.
2021-11-25 BOM and POS file updates
    Working on updating the positioning and BOM files for use with JLCPCB.
2021-11-26 BOM updates
    Updated BOM for JLCPCB with parts changes based on availability. Positioning changes for negative X position on bottom.
2021-12-17 Fix PCB footprint mistake
    There was a mistake with one of the footprints, which was not changed. All footprints are now Alps-compatible and the Gerber files have been updated.
2022-01-21 Updated for 3800 style Capslock
    Added additional footprint for the 3800-style caps lock key. Gerbers updated as well.
2022-01-21 Small silkscreen update
